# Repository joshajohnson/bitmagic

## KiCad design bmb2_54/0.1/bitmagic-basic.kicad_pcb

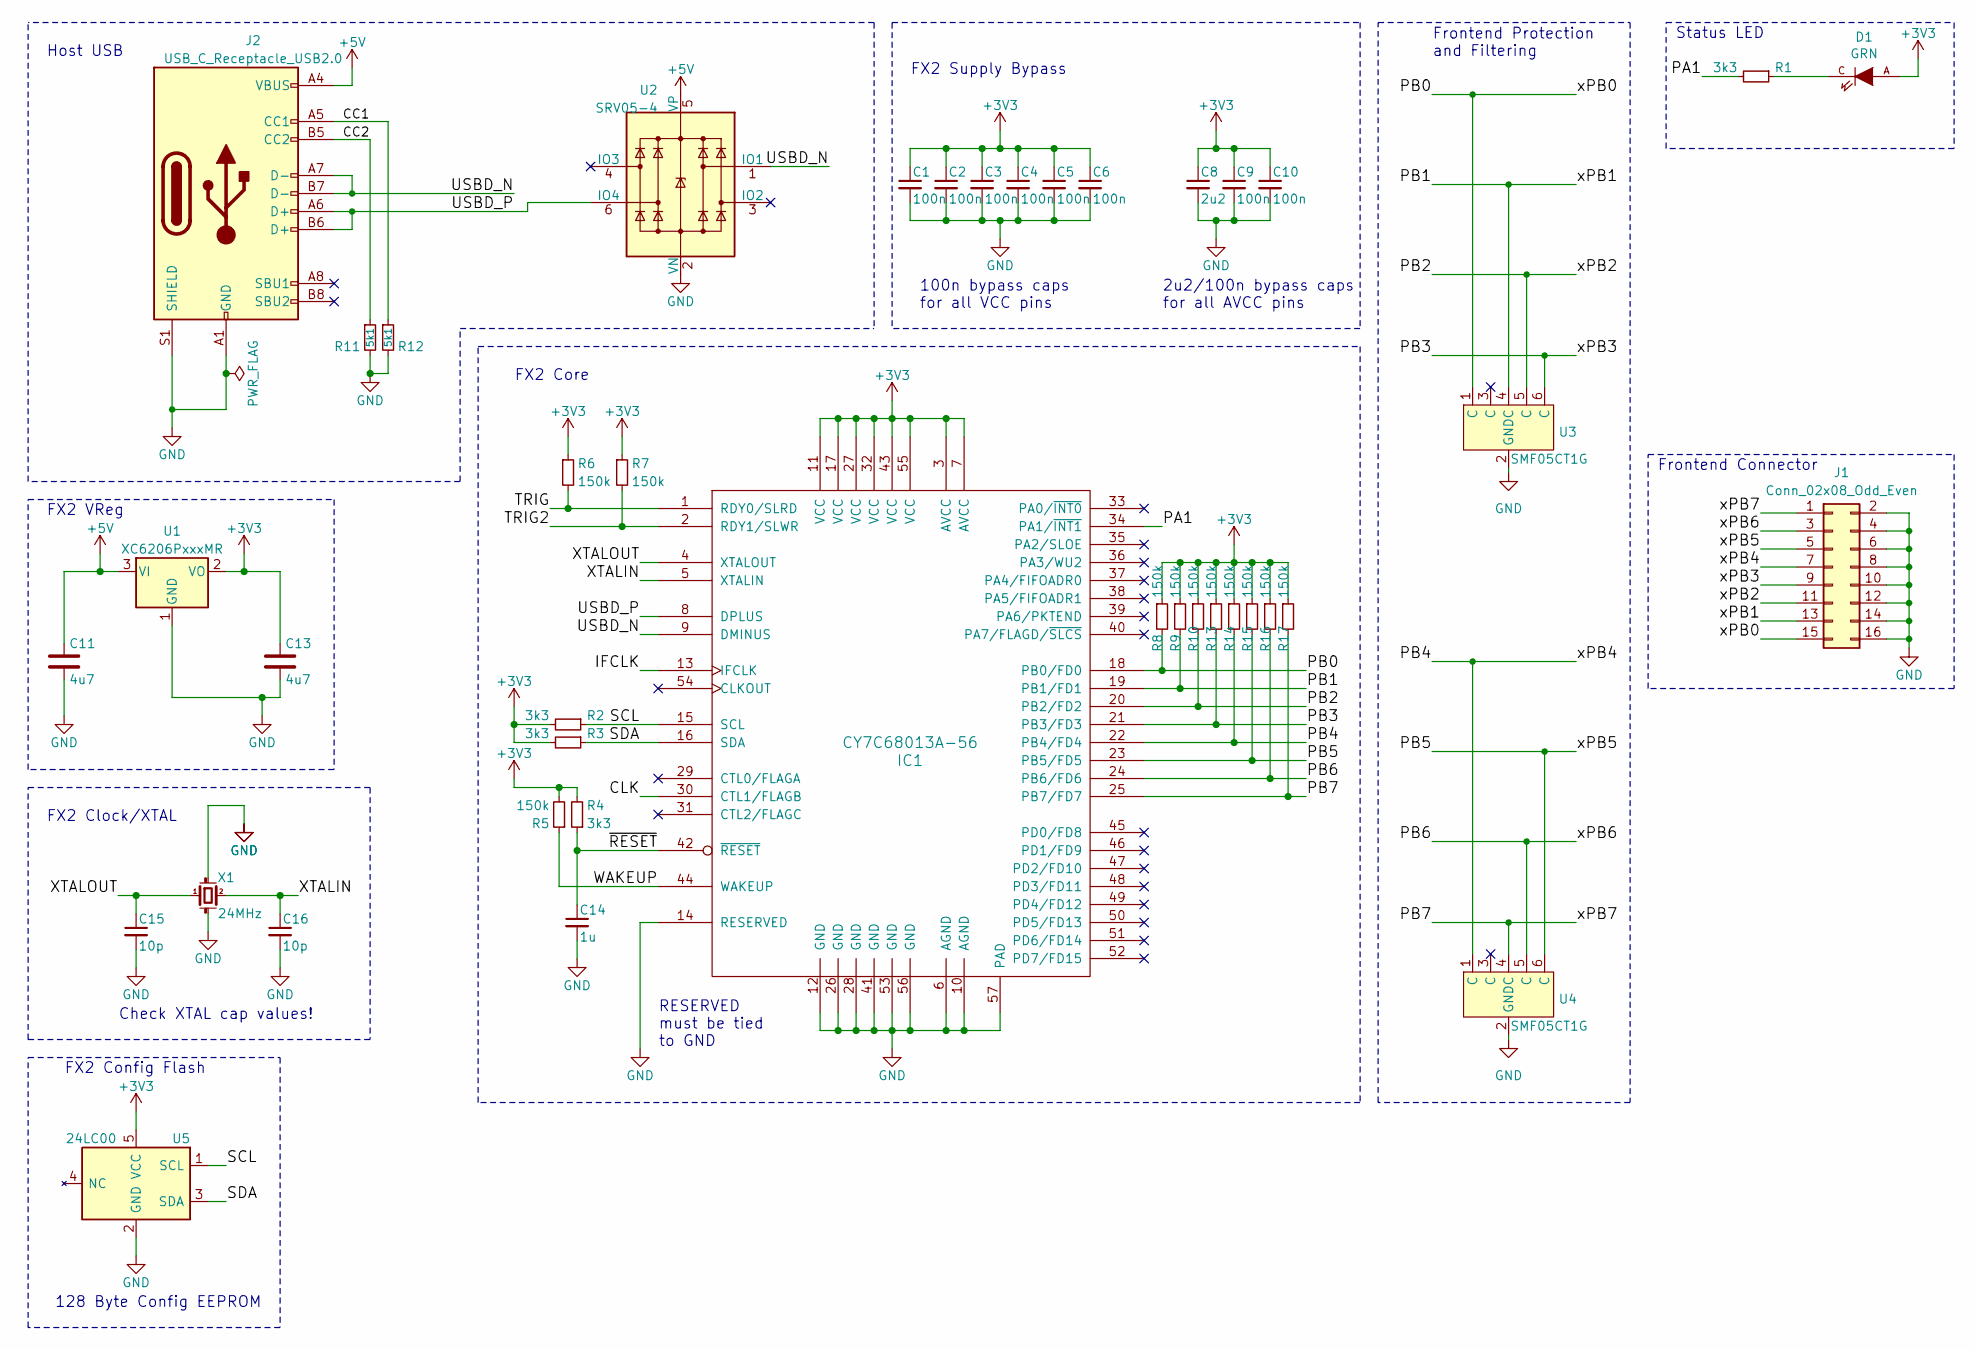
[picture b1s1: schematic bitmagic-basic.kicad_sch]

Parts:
C1, C2, C3, C4, C5, C6, C9, C10: 100n; C_0402; LCSC Part # C307331
C8: 2u2; C_0402; LCSC Part # C12530
C11, C13: 4u7; C_0603; LCSC Part # C19666
C14: 1u; C_0402; LCSC Part # C52923
C15, C16: 10p; C_0402; LCSC Part # C32949
D1: GRN; D_0603; LCSC Part # C72043
IC1: CY7C68013A-56; QFN-56-1EP_8x8mm_Pitch0.5mm; LCSC Part # C14912
J1: Conn_02x08_Odd_Even; PinHeader_2x08_P2.54mm_Horizontal
J2: USB_C_Receptacle_USB2.0; USB_C_Receptacle_HRO_TYPE-C-31-M-12; LCSC Part # C165948
R1, R2, R3, R4: 3k3; R_0402; LCSC Part # C25890
R5, R6, R7, R8, R9, R10, R13, R14, R15, R16, R17: 150k; R_0402; LCSC Part # C25750
R11, R12: 5k1; R_0402; LCSC Part # C25905
U1: XC6206PxxxMR; SOT-23-3; LCSC Part # C5446
U2: SRV05-4; SOT-23-6; LCSC Part # C85364
U3, U4: SMF05CT1G; SOT-363_SC-70-6; LCSC Part # C15879
U5: 24LC00; SOT-23-5; LCSC Part # C84964
X1: 24MHz; ABM8; LCSC Part # C70590

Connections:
+3V3: C1.1, C2.1, C3.1, C4.1, C5.1, C6.1, C8.1, C9.1, C10.1, C13.1, D1.A, IC1.3 (AVCC), IC1.7 (AVCC), IC1.11 (VCC), IC1.17 (VCC), IC1.27 (VCC), IC1.32 (VCC), IC1.43 (VCC), IC1.55 (VCC), R2.2, R3.2, R4.2, R5.2, R6.1, R7.1, R8.1, R9.1, R10.1, R13.1, R14.1, R15.1, R16.1, R17.1, U1.2 (VO), U5.5 (VCC)
+5V: C11.1, J2.A4 (VBUS), J2.A9 (VBUS), J2.B4 (VBUS), J2.B9 (VBUS), U1.3 (VI), U2.5 (VP)
/CC1: J2.A5 (CC1), R12.1
/CC2: J2.B5 (CC2), R11.1
/CLK: IC1.30 (CTL1/FLAGB)
/IFCLK: IC1.13 (IFCLK)
/PA1: IC1.34 (PA1/~INT1), R1.2
/PB0: IC1.18 (PB0/FD0), J1.15, R8.2, U3.1 (C)
/PB1: IC1.19 (PB1/FD1), J1.13, R9.2, U3.4 (C)
/PB2: IC1.20 (PB2/FD2), J1.11, R10.2, U3.5 (C)
/PB3: IC1.21 (PB3/FD3), J1.9, R13.2, U3.6 (C)
/PB4: IC1.22 (PB4/FD4), J1.7, R14.2, U4.1 (C)
/PB5: IC1.23 (PB5/FD5), J1.5, R15.2, U4.6 (C)
/PB6: IC1.24 (PB6/FD6), J1.3, R16.2, U4.5 (C)
/PB7: IC1.25 (PB7/FD7), J1.1, R17.2, U4.4 (C)
/SCL: IC1.15 (SCL), R2.1, U5.1 (SCL)
/SDA: IC1.16 (SDA), R3.1, U5.3 (SDA)
/TRIG: IC1.1 (RDY0/SLRD), R6.2
/TRIG2: IC1.2 (RDY1/SLWR), R7.2
/USBD_N: IC1.9 (DMINUS), J2.A7 (D-), J2.B7 (D-), U2.1 (IO1)
/USBD_P: IC1.8 (DPLUS), J2.A6 (D+), J2.B6 (D+), U2.6 (IO4)
/WAKEUP: IC1.44 (WAKEUP), R5.1
/XTALIN: C16.1, IC1.5 (XTALIN), X1.2
/XTALOUT: C15.1, IC1.4 (XTALOUT), X1.1
/~RESET: C14.1, IC1.42 (~RESET), R4.1
GND: C1.2, C2.2, C3.2, C4.2, C5.2, C6.2, C8.2, C9.2, C10.2, C11.2, C13.2, C14.2, C15.2, C16.2, IC1.6 (AGND), IC1.10 (AGND), IC1.12 (GND), IC1.14 (RESERVED), IC1.26 (GND), IC1.28 (GND), IC1.41 (GND), IC1.53 (GND), IC1.56 (GND), IC1.57 (PAD), J1.2, J1.4, J1.6, J1.8, J1.10, J1.12, J1.14, J1.16, J2.A1 (GND), J2.A12 (GND), J2.B1 (GND), J2.B12 (GND), J2.S1 (SHIELD), R11.2, R12.2, U1.1 (GND), U2.2 (VN), U3.2 (GND), U4.2 (GND), U5.2 (GND), X1.GND (case)
unnamed: D1.C, R1.1

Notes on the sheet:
100n bypass caps for all VCC pins
Host USB
Check XTAL cap values!
FX2 Config Flash
Frontend Protection and Filtering
FX2 Supply Bypass
2u2/100n bypass caps for all AVCC pins
FX2 Core
Frontend Connector
FX2 Clock/XTAL
FX2 VReg
Status LED
128 Byte Config EEPROM
RESERVED must be tied to GND

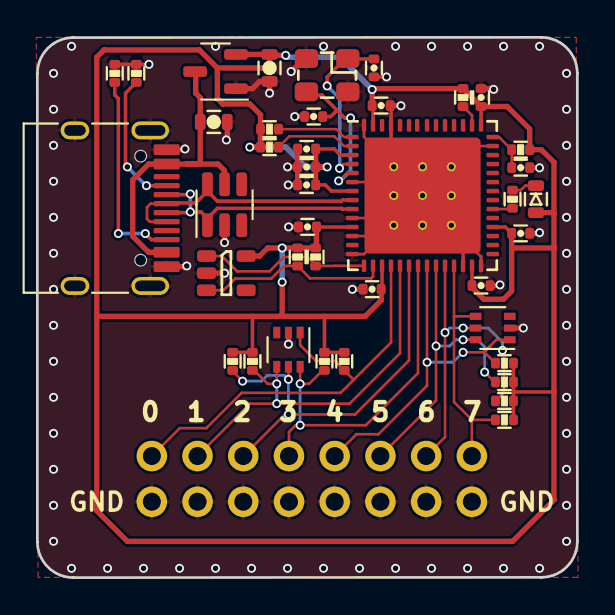
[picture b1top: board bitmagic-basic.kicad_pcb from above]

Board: 2 copper layers, 30.0 x 30.0 mm, 41 parts (0 on the bottom side), 25 nets.

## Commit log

2023-09-21 add 2.54mm version of bmb

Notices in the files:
bmb2_54/0.1/bitmagic-basic.kicad_pcb:
CC-BY-SA V4.0
(C) 2019 1BitSquared
(C) 2019 Piotr Esden-Tempski
CC-BY-SA 4.0
bmb2_54/0.1/bitmagic-basic.kicad_sch:
License: CC-BY-SA V4.0
(C) 2019-2020 1BitSquared
(C) 2019-2020 Piotr Esden-Tempski
